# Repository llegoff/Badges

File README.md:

# Badges

Buy on Ebay 
 
 Calavera PCB : https://www.ebay.fr/itm/153633710557

 Unicorn PCB : https://www.ebay.fr/itm/153633723346

PCB Badges

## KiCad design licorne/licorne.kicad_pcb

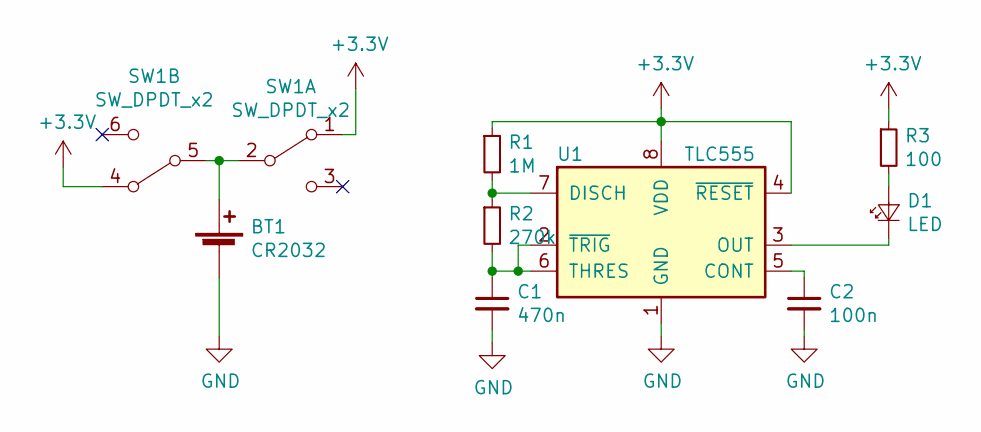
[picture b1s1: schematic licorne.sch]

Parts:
BT1: CR2032; CR2032_smd
C1: 470n; C_0805_HandSoldering
C2: 100n; C_0805_HandSoldering
D1: LED; LED_0805_HandSoldering
R1: 1M; R_0805_HandSoldering
R2: 270k; R_0805_HandSoldering
R3: 100; R_0805_HandSoldering
SW1: SW_DPDT_x2; SW_DPDT_MSS22D18
U1: TLC555; SOIC-8_3.9x4.9mm_Pitch1.27mm

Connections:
+3V3: R1.1, R3.1, SW1.1 (A), SW1.4 (A), U1.4 (~RESET), U1.8 (VDD)
GND: BT1.2 (-), C1.2, C2.2, U1.1 (GND)
unnamed: BT1.1 (+), SW1.2 (B), SW1.5 (B)
unnamed: C1.1, R2.2, U1.2 (~TRIG), U1.6 (THRES)
unnamed: C2.1, U1.5 (CONT)
unnamed: D1.1 (K), U1.3 (OUT)
unnamed: D1.2 (A), R3.2
unnamed: R1.2, R2.1, U1.7 (DISCH)

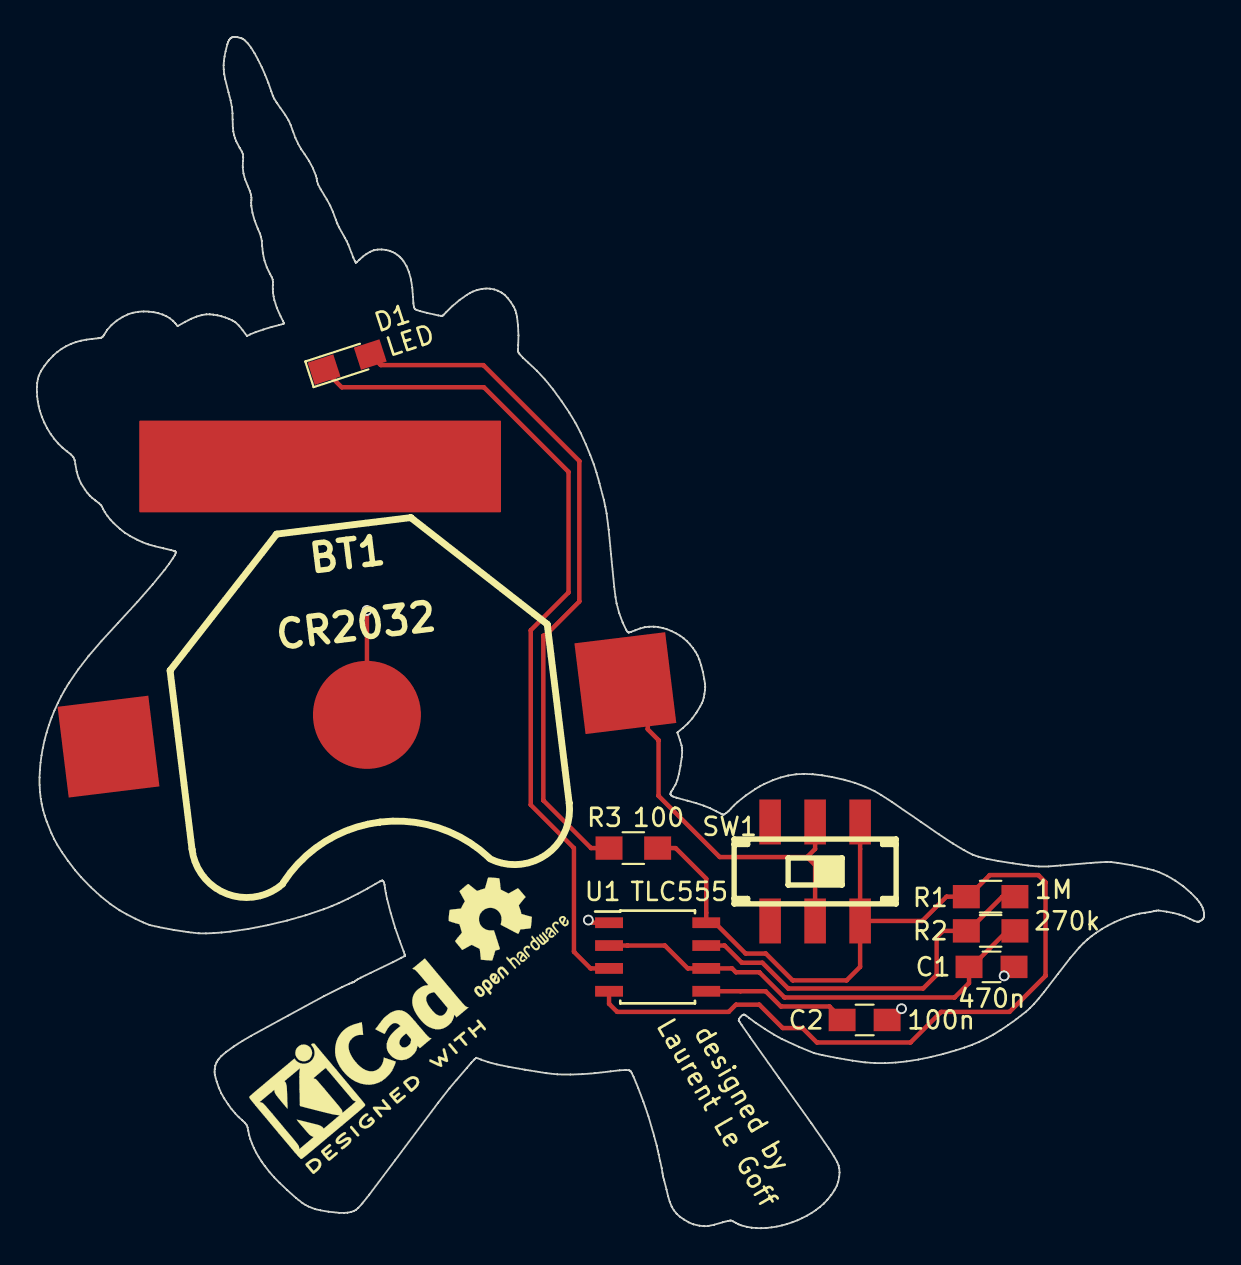
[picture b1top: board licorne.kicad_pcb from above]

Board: 2 copper layers, 64.8 x 66.2 mm, 9 parts (0 on the bottom side), 8 nets.

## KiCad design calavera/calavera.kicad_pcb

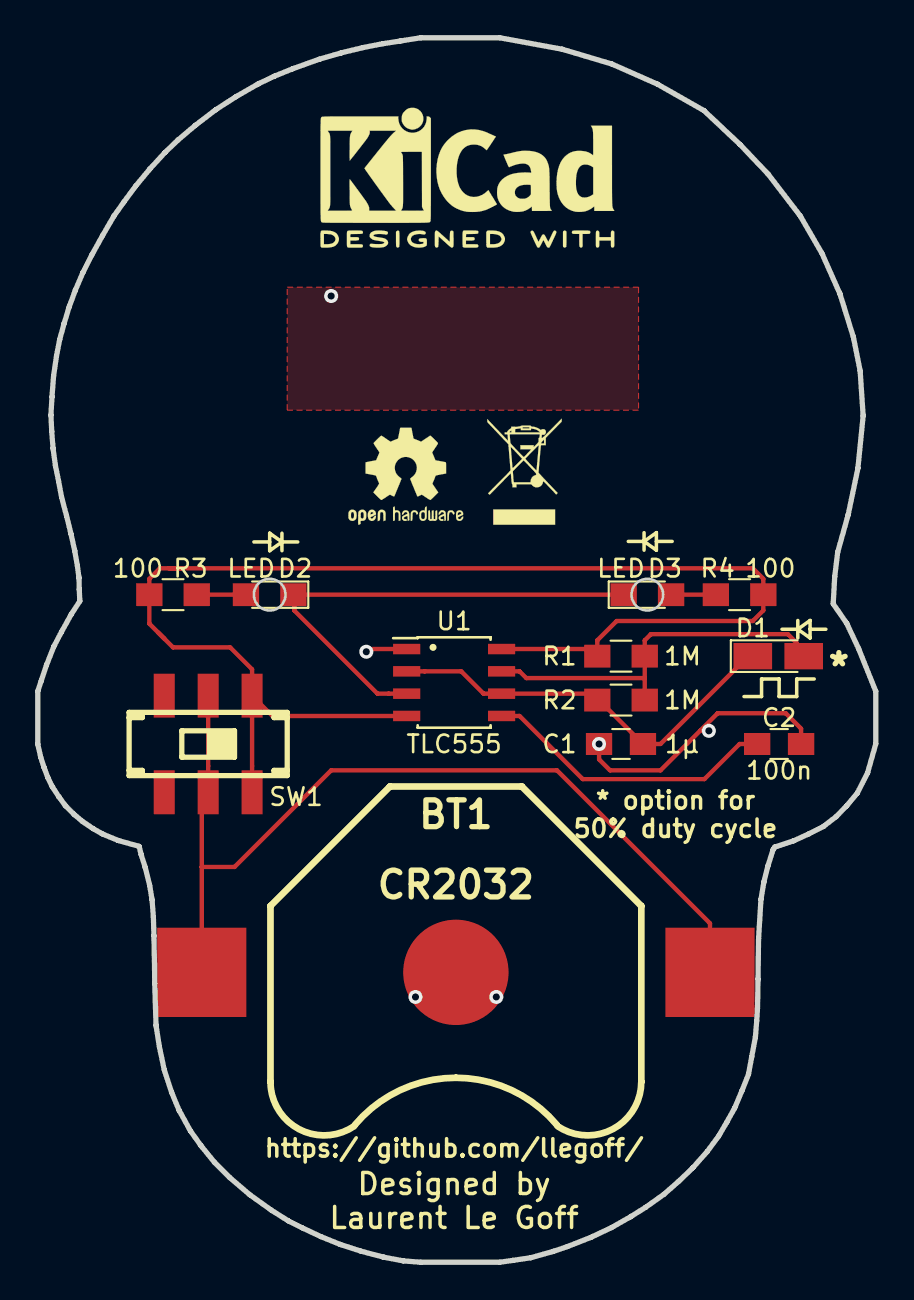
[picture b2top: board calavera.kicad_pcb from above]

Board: 2 copper layers, 47.7 x 69.7 mm, 12 parts (0 on the bottom side), 9 nets.

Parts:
BT1: CR2032; CR2032_smd
C1: 1µ; C_0805_HandSoldering
C2: 100n; C_0805_HandSoldering
D1: 1N4148; D_MicroMELF_Hadsoldering
D2, D3: LED; LED_0805_HandSoldering
R1, R2: 1M; R_0805_HandSoldering
R3, R4: 100; R_0805_HandSoldering
SW1: SW_DPDT_x2; SW_DPDT_MSS22D18
U1: TLC555; SOIC-8_3.9x4.9mm_Pitch1.27mm

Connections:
+3V3: R1.1, R3.1, R4.1, SW1.1, SW1.4, U1.4, U1.8
GND: BT1.2, C1.2, C2.2, U1.1
unnamed: BT1.1, SW1.2, SW1.5
unnamed: C1.1, D1.1, R2.2, U1.2, U1.6
unnamed: C2.1, U1.5
unnamed: D1.2, R1.2, R2.1, U1.7
unnamed: D2.1, D3.1, U1.3
unnamed: D2.2, R3.2
unnamed: D3.2, R4.2
